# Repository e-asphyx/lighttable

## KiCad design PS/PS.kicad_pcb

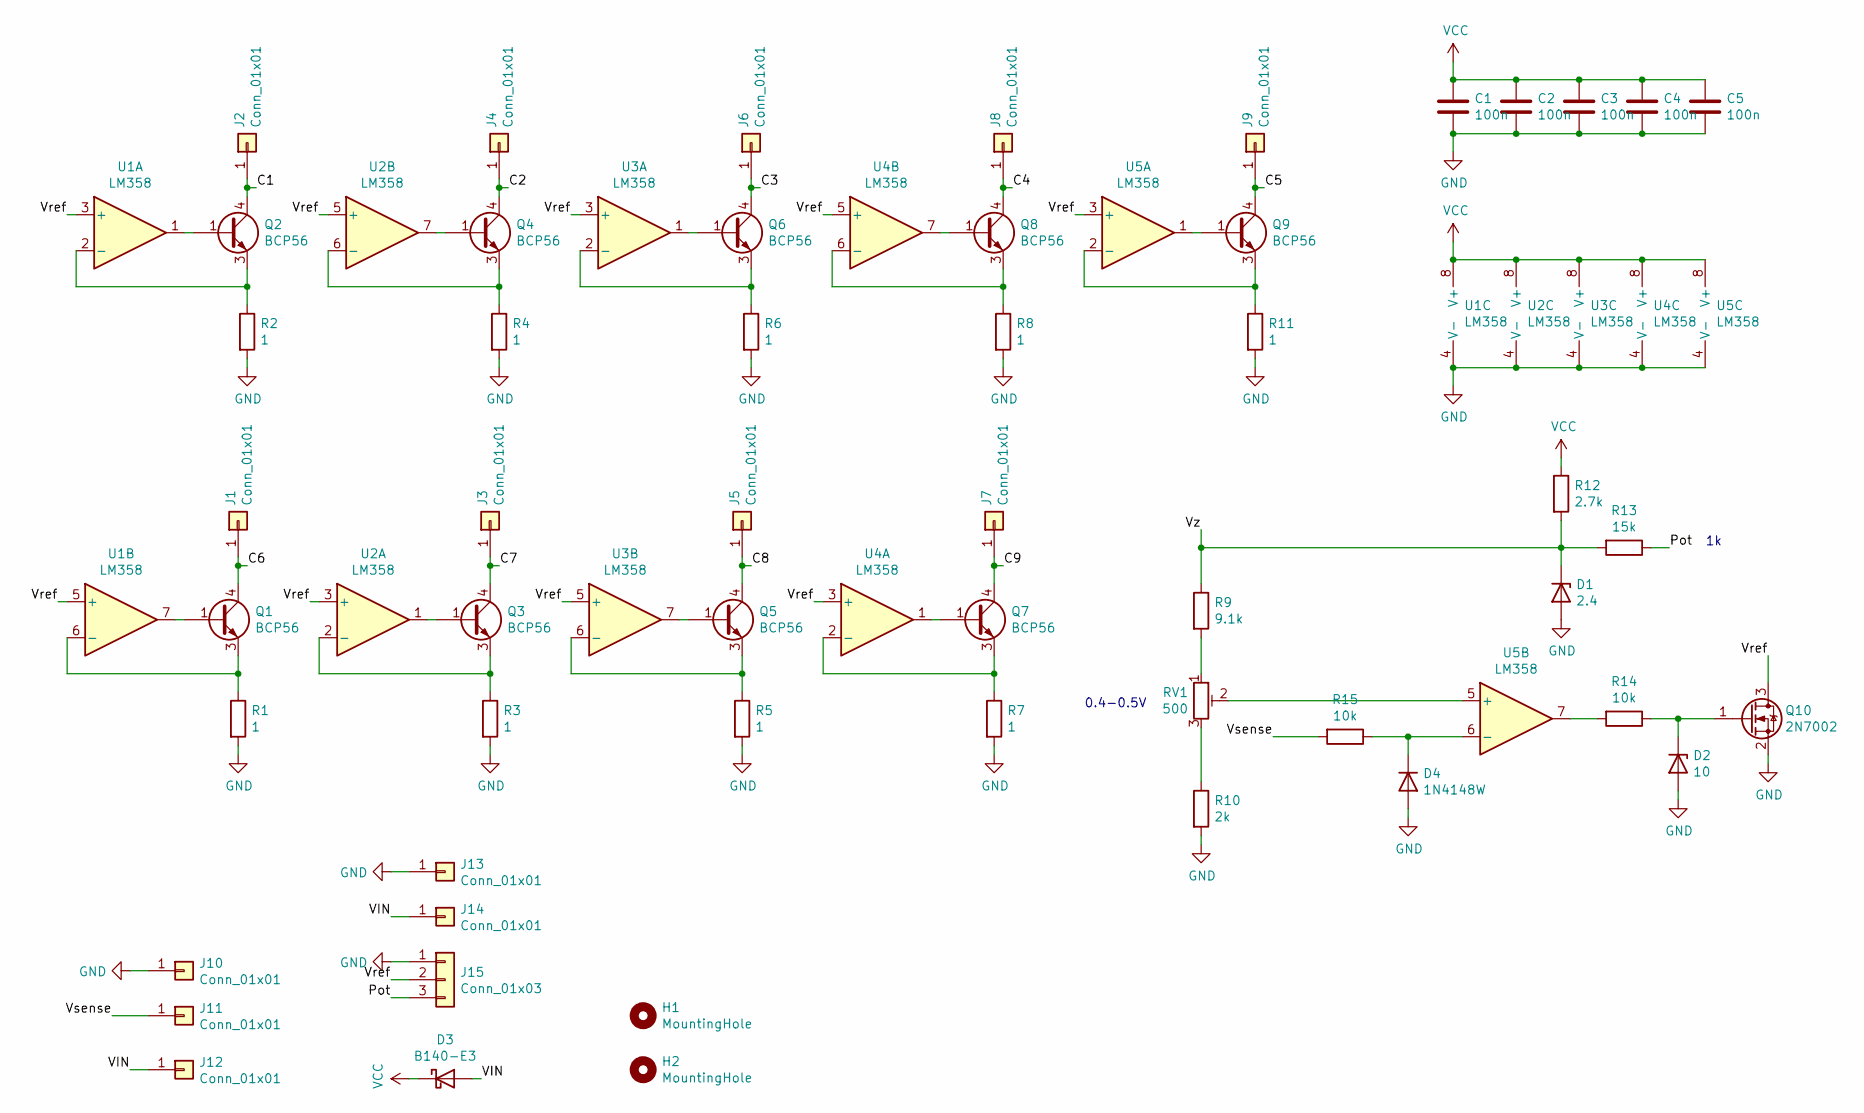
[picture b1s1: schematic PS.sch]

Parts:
C1, C2, C3, C4, C5: 100n; C_0805_2012Metric
D1: 2.4; D_SOD-123
D2: 10; D_SOD-123
D3: B140-E3; D_SMA
D4: 1N4148W; D_SOD-123
H1, H2: MountingHole; MountingHole_3.2mm_M3
J1, J2, J3, J4, J5, J6, J7, J8, J9, J10, J11: Conn_01x01; SolderWire-0.5sqmm_1x01_D0.9mm_OD2.1mm
J12, J13, J14: Conn_01x01; SolderWire-0.75sqmm_1x01_D1.25mm_OD2.3mm
J15: Conn_01x03; PinHeader_1x03_P2.54mm_Vertical
Q1, Q2, Q3, Q4, Q5, Q6, Q7, Q8, Q9: BCP56; SOT-223
Q10: 2N7002; SOT-23
R1, R2, R3, R4, R5, R6, R7, R8, R11: 1; R_1210_3225Metric
R9: 9.1k; R_0805_2012Metric
R10: 2k; R_0805_2012Metric
R12: 2.7k; R_0805_2012Metric
R13: 15k; R_0805_2012Metric
R14, R15: 10k; R_0805_2012Metric
RV1: 500; Potentiometer_Bourns_3214W_Vertical
U1, U2, U3, U4, U5: LM358; SOIC-8_3.9x4.9mm_P1.27mm

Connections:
/C1: J2.1, Q2.4 (C)
/C2: J4.1, Q4.4 (C)
/C3: J6.1, Q6.4 (C)
/C4: J8.1, Q8.4 (C)
/C5: J9.1, Q9.4 (C)
/C6: J1.1, Q1.4 (C)
/C7: J3.1, Q3.4 (C)
/C8: J5.1, Q5.4 (C)
/C9: J7.1, Q7.4 (C)
/Pot: J15.3, R13.1
/VIN: D3.2 (A), J12.1, J14.1
/Vref: J15.2, Q10.3 (D), U1.3 (+), U1.5 (+), U2.3 (+), U2.5 (+), U3.3 (+), U3.5 (+), U4.3 (+), U4.5 (+), U5.3 (+)
/Vsense: J11.1, R15.2
/Vz: D1.1 (K), R9.1, R12.2, R13.2
GND: C1.2, C2.2, C3.2, C4.2, C5.2, D1.2 (A), D2.2 (A), D4.2 (A), J10.1, J13.1, J15.1, Q10.2 (S), R1.2, R2.2, R3.2, R4.2, R5.2, R6.2, R7.2, R8.2, R10.2, R11.2, U1.4 (V-), U2.4 (V-), U3.4 (V-), U4.4 (V-), U5.4 (V-)
unnamed: D2.1 (K), Q10.1 (G), R14.1
unnamed: D4.1 (K), R15.1, U5.6 (-)
unnamed: Q1.1 (B), U1.7
unnamed: Q1.3 (E), R1.1, U1.6 (-)
unnamed: Q2.1 (B), U1.1
unnamed: Q2.3 (E), R2.1, U1.2 (-)
unnamed: Q3.1 (B), U2.1
unnamed: Q3.3 (E), R3.1, U2.2 (-)
unnamed: Q4.1 (B), U2.7
unnamed: Q4.3 (E), R4.1, U2.6 (-)
unnamed: Q5.1 (B), U3.7
unnamed: Q5.3 (E), R5.1, U3.6 (-)
unnamed: Q6.1 (B), U3.1
unnamed: Q6.3 (E), R6.1, U3.2 (-)
unnamed: Q7.1 (B), U4.1
unnamed: Q7.3 (E), R7.1, U4.2 (-)
unnamed: Q8.1 (B), U4.7
unnamed: Q8.3 (E), R8.1, U4.6 (-)
unnamed: Q9.1 (B), U5.1
unnamed: Q9.3 (E), R11.1, U5.2 (-)
unnamed: R9.2, RV1.1
unnamed: R10.1, RV1.3
unnamed: R14.2, U5.7
unnamed: RV1.2, U5.5 (+)
VCC: C1.1, C2.1, C3.1, C4.1, C5.1, D3.1 (K), R12.1, U1.8 (V+), U2.8 (V+), U3.8 (V+), U4.8 (V+), U5.8 (V+)

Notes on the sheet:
0.4-0.5V

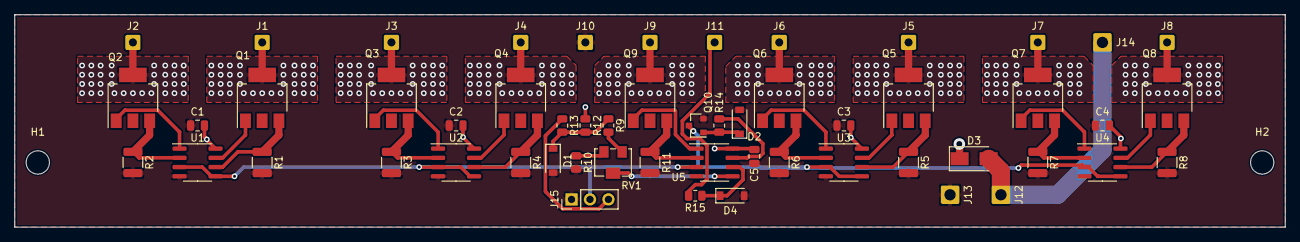
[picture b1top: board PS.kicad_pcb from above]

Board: 2 copper layers, 174.8 x 29.2 mm, 57 parts (0 on the bottom side), 40 nets.

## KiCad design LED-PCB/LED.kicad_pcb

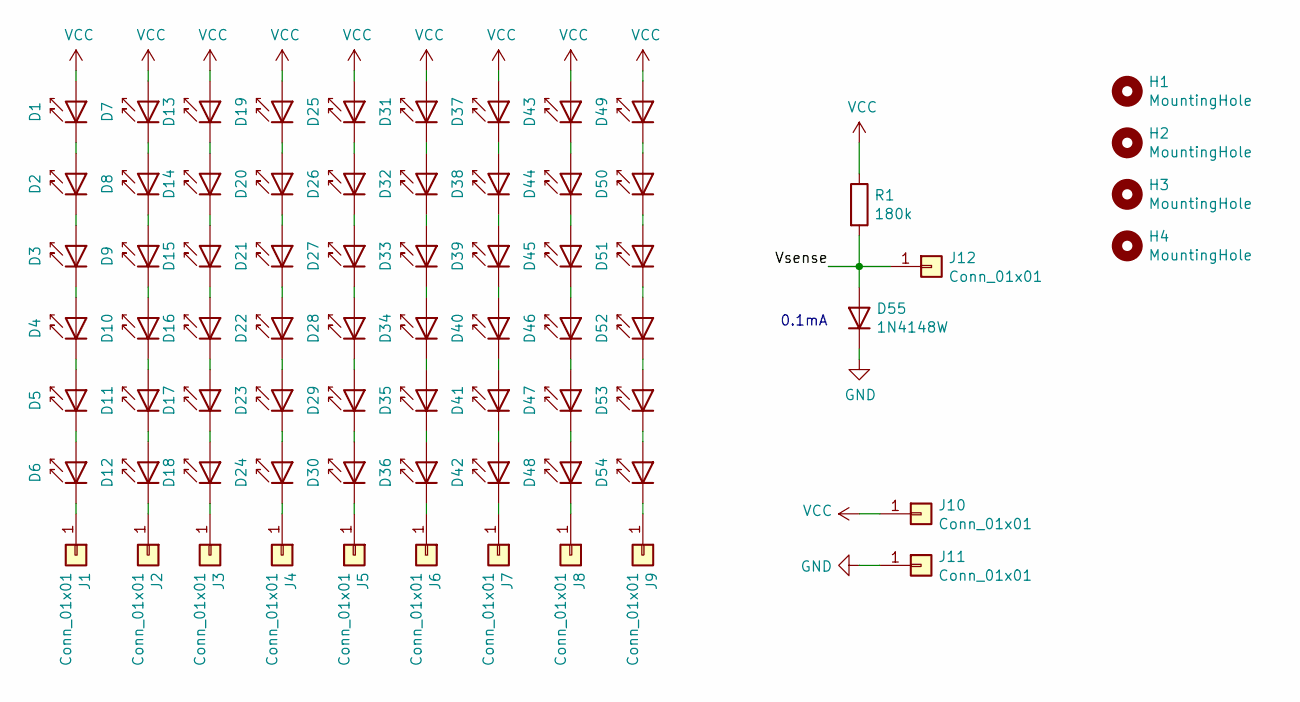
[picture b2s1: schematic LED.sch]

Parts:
D1, D2, D3, D4, D5, D6, D7, D8, D9, D10, D11, D12, D13, D14, D15, D16, D17, D18, D19, D20, D21, D22, D23, D24, D25, D26, D27, D28, D29, D30, D31, D32, D33, D34, D35, D36, D37, D38, D39, D40, D41, D42, D43, D44, D45, D46, D47, D48, D49, D50, D51, D52, D53, D54: BXEN-50S-11M-3C; LED_PLCC_2835
D55: 1N4148W; D_SOD-123
H1, H2, H3, H4: MountingHole; MountingHole_3.2mm_M3
J1, J2, J3, J4, J5, J6, J7, J8, J9, J11, J12: Conn_01x01; Pad-2.5x5
J10: Conn_01x01; Pad-5x10
R1: 180k; R_0805_2012Metric

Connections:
/Vsense: D55.2 (A), J12.1, R1.2
GND: D55.1 (K), J11.1
unnamed: D1.1 (K), D2.2 (A)
unnamed: D2.1 (K), D3.2 (A)
unnamed: D3.1 (K), D4.2 (A)
unnamed: D4.1 (K), D5.2 (A)
unnamed: D5.1 (K), D6.2 (A)
unnamed: D6.1 (K), J1.1
unnamed: D7.1 (K), D8.2 (A)
unnamed: D8.1 (K), D9.2 (A)
unnamed: D10.1 (K), D11.2 (A)
unnamed: D9.1 (K), D10.2 (A)
unnamed: D11.1 (K), D12.2 (A)
unnamed: D12.1 (K), J2.1
unnamed: D13.1 (K), D14.2 (A)
unnamed: D14.1 (K), D15.2 (A)
unnamed: D15.1 (K), D16.2 (A)
unnamed: D16.1 (K), D17.2 (A)
unnamed: D17.1 (K), D18.2 (A)
unnamed: D18.1 (K), J3.1
unnamed: D19.1 (K), D20.2 (A)
unnamed: D20.1 (K), D21.2 (A)
unnamed: D21.1 (K), D22.2 (A)
unnamed: D22.1 (K), D23.2 (A)
unnamed: D23.1 (K), D24.2 (A)
unnamed: D24.1 (K), J4.1
unnamed: D25.1 (K), D26.2 (A)
unnamed: D26.1 (K), D27.2 (A)
unnamed: D27.1 (K), D28.2 (A)
unnamed: D28.1 (K), D29.2 (A)
unnamed: D29.1 (K), D30.2 (A)
unnamed: D30.1 (K), J5.1
unnamed: D31.1 (K), D32.2 (A)
unnamed: D32.1 (K), D33.2 (A)
unnamed: D33.1 (K), D34.2 (A)
unnamed: D34.1 (K), D35.2 (A)
unnamed: D35.1 (K), D36.2 (A)
unnamed: D36.1 (K), J6.1
unnamed: D37.1 (K), D38.2 (A)
unnamed: D38.1 (K), D39.2 (A)
unnamed: D39.1 (K), D40.2 (A)
unnamed: D40.1 (K), D41.2 (A)
unnamed: D41.1 (K), D42.2 (A)
unnamed: D42.1 (K), J7.1
unnamed: D43.1 (K), D44.2 (A)
unnamed: D44.1 (K), D45.2 (A)
unnamed: D45.1 (K), D46.2 (A)
unnamed: D46.1 (K), D47.2 (A)
unnamed: D47.1 (K), D48.2 (A)
unnamed: D48.1 (K), J8.1
unnamed: D49.1 (K), D50.2 (A)
unnamed: D50.1 (K), D51.2 (A)
unnamed: D51.1 (K), D52.2 (A)
unnamed: D52.1 (K), D53.2 (A)
unnamed: D53.1 (K), D54.2 (A)
unnamed: D54.1 (K), J9.1
VCC: D1.2 (A), D7.2 (A), D13.2 (A), D19.2 (A), D25.2 (A), D31.2 (A), D37.2 (A), D43.2 (A), D49.2 (A), J10.1, R1.1

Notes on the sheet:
0.1mA

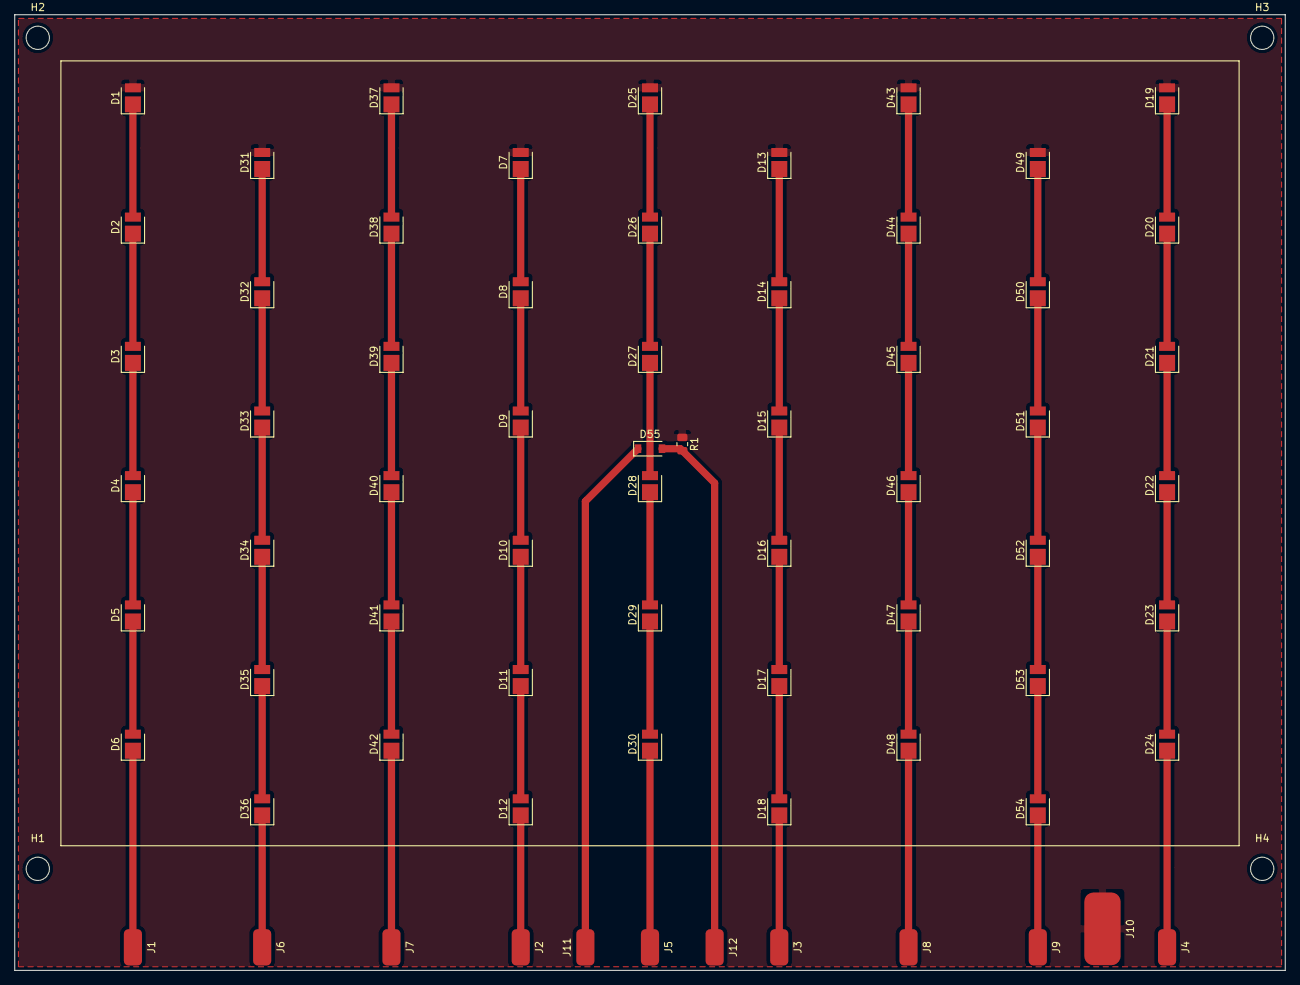
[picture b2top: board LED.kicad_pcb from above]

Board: 2 copper layers, 174.8 x 131.4 mm, 72 parts (0 on the bottom side), 57 nets.

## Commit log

2021-12-02 Initial
2021-12-16 Shared libraries
2021-12-22 Incorrect value
2021-12-23 Vce saturation voltage is too hight, use MOSFET as a switch
2021-12-23 More fixes (magic smoke happened)
2021-12-23 protect sense input
